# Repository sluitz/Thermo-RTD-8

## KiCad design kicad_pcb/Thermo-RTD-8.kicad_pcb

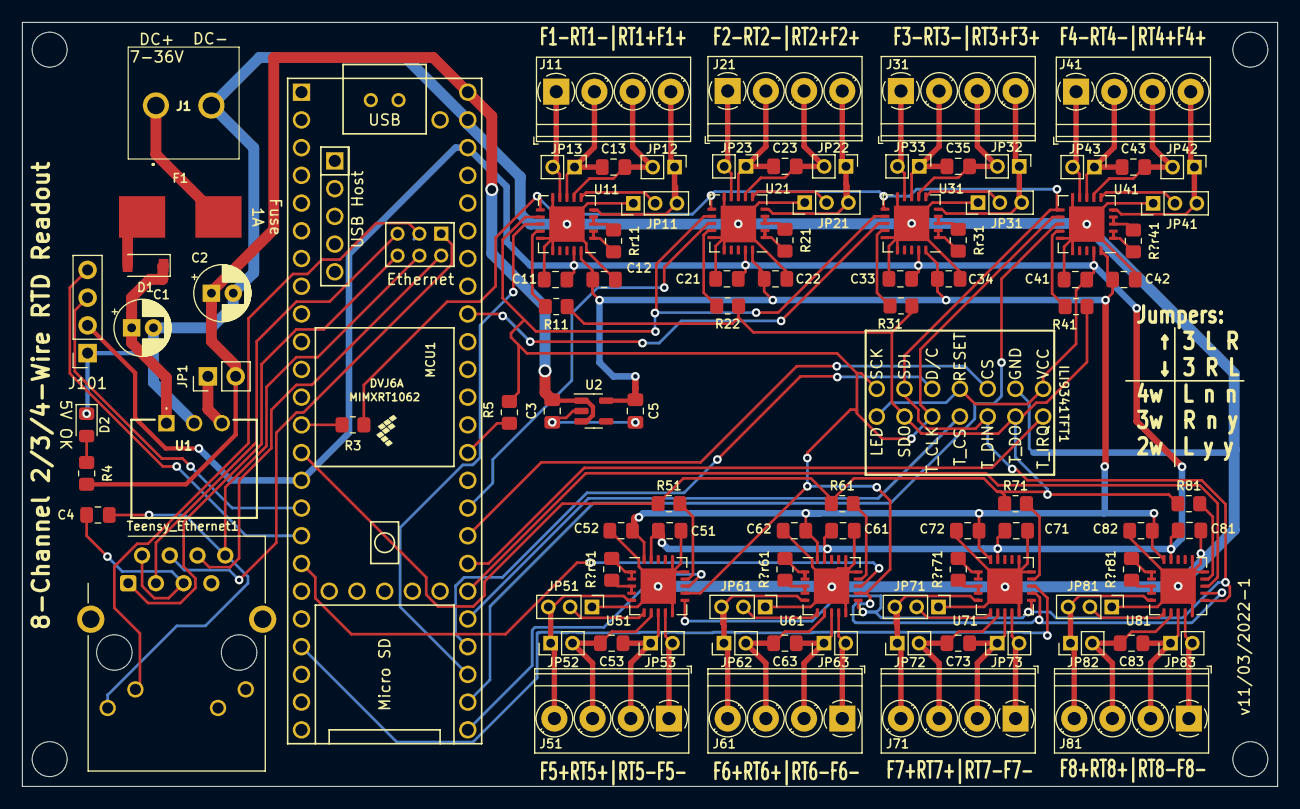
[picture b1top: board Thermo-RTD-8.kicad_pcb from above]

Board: 2 copper layers, 115.0 x 70.0 mm, 103 parts (0 on the bottom side), 99 nets.

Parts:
C1: 10u; CP_Radial_D5.0mm_P2.00mm
C2: 22u; CP_Radial_D5.0mm_P2.00mm
C3, C5: 1u; C_0805_2012Metric_Pad1.18x1.45mm_HandSolder
C4, C11, C12, C13, C21, C22, C23, C33, C34, C35, C41, C42, C43, C51, C52, C53, C61, C62, C63, C71, C72, C73, C81, C82, C83: 100n; C_0805_2012Metric_Pad1.18x1.45mm_HandSolder
D1: D; D_SOD-123
D2: LED 5VOK; LED_0805_2012Metric_Pad1.15x1.40mm_HandSolder
F1: 1A; smd_fuse
H1, H2, H3, H4: MountingHole; MountingHole_3.2mm_M3_DIN965
ILI9341TFT1: ILI9341TFT-RibbonCable
J1: Screw_Terminal_01x02; TB00750802BE
J11, J21, J31, J41, J51, J61, J71, J81: Ch1; TerminalBlock_Phoenix_PT-1,5-4-3.5-H_1x04_P3.50mm_Horizontal
J101: OLED Display I2C; PinSocket_1x04_P2.54mm_Vertical
JP1: PS; PinHeader_1x02_P2.54mm_Vertical
JP11, JP21, JP31, JP41, JP51, JP61, JP71, JP81: 3w:2+3; PinHeader_1x03_P2.00mm_Vertical
JP12, JP22, JP32, JP42, JP52, JP62, JP72, JP82: 2w; PinHeader_1x02_P2.00mm_Vertical
JP13, JP23, JP33, JP43, JP53, JP63, JP73, JP83: 2/3w; PinHeader_1x02_P2.00mm_Vertical
MCU1: Teensy41
R3, R5, R11, R22, R31, R41, R51, R61, R71, R81: 22R; R_0805_2012Metric_Pad1.20x1.40mm_HandSolder
R4: 330R; R_0805_2012Metric_Pad1.20x1.40mm_HandSolder
R21: 440R; R_0805_2012Metric_Pad1.20x1.40mm_HandSolder
R?r41, R?r51, R?r61, R?r71, R?r81: 440R; R_0805_2012Metric_Pad1.20x1.40mm_HandSolder
Rr11, Rr31: 440R; R_0805_2012Metric_Pad1.20x1.40mm_HandSolder
Teensy_Ethernet1: RJ45_Cetus_J1B1211CCD_Horizontal
U1: N7805; N78051C
U2: NCP163ASN330T1G; SOT-23-5
U11, U21, U31, U41, U51, U61, U71, U81: MAX31865xTP; TQFN-20-1EP_5x5mm_P0.65mm_EP3.25x3.25mm

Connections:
+3.3V: C11.2, C21.2, C33.2, C41.2, C51.2, C61.2, C71.2, C81.2, ILI9341TFT1.1, ILI9341TFT1.4, ILI9341TFT1.8, J101.2, MCU1.15 (3V3), MCU1.46 (3V3), U11.19 (DVDD), U21.19 (DVDD), U31.19 (DVDD), U41.19 (DVDD), U51.19 (DVDD), U61.19 (DVDD), U71.19 (DVDD), U81.19 (DVDD)
+3.3VA: C5.1, C12.1, C22.1, C34.1, C42.1, C52.1, C62.1, C72.1, C82.1, U2.5 (VOUT), U11.20 (VDD), U21.20 (VDD), U31.20 (VDD), U41.20 (VDD), U51.20 (VDD), U61.20 (VDD), U71.20 (VDD), U81.20 (VDD)
+5V: C2.1, C3.1, JP1.2 (B), MCU1.48 (VIN), R4.1, U2.1 (VIN), U2.3 (EN)
/CLK: ILI9341TFT1.7, ILI9341TFT1.10, R5.1, U11.12 (SCLK), U21.12 (SCLK), U31.12 (SCLK), U41.12 (SCLK), U51.12 (SCLK), U61.12 (SCLK), U71.12 (SCLK), U81.12 (SCLK)
/CS_1: MCU1.27 (35_TX8), U11.13 (~CS)
/CS_2: MCU1.33 (41_A17), U21.13 (~CS)
/CS_3: MCU1.40 (18_A4_SDA), U31.13 (~CS)
/CS_4: MCU1.26 (34_RX8), U41.13 (~CS)
/CS_5: MCU1.25 (33_MCLK2), U51.13 (~CS)
/CS_6: MCU1.18 (26_A12_MOSI1), U61.13 (~CS)
/CS_7: MCU1.21 (29_TX7), U71.13 (~CS)
/CS_8: MCU1.30 (38_CS1_IN1), U81.13 (~CS)
/SDI: ILI9341TFT1.6, ILI9341TFT1.12, R3.2, U11.11 (SDI), U21.11 (SDI), U31.11 (SDI), U41.11 (SDI), U51.11 (SDI), U61.11 (SDI), U71.11 (SDI), U81.11 (SDI)
/SDO: ILI9341TFT1.9, ILI9341TFT1.13, MCU1.14 (12_MISO_MQSL), R11.1, R22.1, R31.1, R41.1, R51.1, R61.1, R71.1, R81.1
/TFT_CS: ILI9341TFT1.3, MCU1.32 (40_A16)
/TFT_DC: ILI9341TFT1.5, MCU1.28 (36_CS)
/T_CS: ILI9341TFT1.11, MCU1.29 (37_CS)
/T_IRQ: ILI9341TFT1.14, MCU1.31 (39_MISO1_OUT1A)
GND: C1.2, C2.2, C3.2, C5.2, C11.1, C12.2, C21.1, C22.2, C33.1, C34.2, C41.1, C42.2, C51.1, C52.2, C61.1, C62.2, C71.1, C72.2, C81.1, C82.2, D2.1 (K), ILI9341TFT1.2, J1.2, J101.1, JP11.1 (A), JP21.1 (A), JP31.1 (A), JP41.1 (A), JP51.1 (A), JP61.1 (A), JP71.1 (A), JP81.1 (A), MCU1.47 (GND), U1.2 (GND/-Vout), U2.2 (GND), U11.10 (GND), U11.15 (DGND), U11.16 (GND), U11.21 (GND), U21.10 (GND), U21.15 (DGND), U21.16 (GND), U21.21 (GND), U31.10 (GND), U31.15 (DGND), U31.16 (GND), U31.21 (GND), U41.10 (GND), U41.15 (DGND), U41.16 (GND), U41.21 (GND), U51.10 (GND), U51.15 (DGND), U51.16 (GND), U51.21 (GND), U61.10 (GND), U61.15 (DGND), U61.16 (GND), U61.21 (GND), U71.10 (GND), U71.15 (DGND), U71.16 (GND), U71.21 (GND), U81.10 (GND), U81.15 (DGND), U81.16 (GND), U81.21 (GND)
I2C_SCL: J101.3, MCU1.16 (24_A10_TX6_SCL2)
I2C_SDA: J101.4, MCU1.17 (25_A11_RX6_SDA2)
unnamed: C1.1, D1.1 (K), U1.1 (IN)
unnamed: C4.1, Teensy_Ethernet1.2, Teensy_Ethernet1.5
unnamed: C4.2, MCU1.64 (GND), Teensy_Ethernet1.8, Teensy_Ethernet1.9
unnamed: C13.1, J11.2, JP13.1 (A), U11.8 (RTDIN-)
unnamed: C13.2, J11.3, JP12.2 (B), U11.7 (RTDIN+)
unnamed: C23.1, J21.2, JP23.1 (A), U21.8 (RTDIN-)
unnamed: C23.2, J21.3, JP22.2 (B), U21.7 (RTDIN+)
unnamed: C35.1, J31.2, JP33.1 (A), U31.8 (RTDIN-)
unnamed: C35.2, J31.3, JP32.2 (B), U31.7 (RTDIN+)
unnamed: C43.1, J41.2, JP43.1 (A), U41.8 (RTDIN-)
unnamed: C43.2, J41.3, JP42.2 (B), U41.7 (RTDIN+)
unnamed: C53.1, J51.2, JP53.1 (A), U51.8 (RTDIN-)
unnamed: C53.2, J51.3, JP52.2 (B), U51.7 (RTDIN+)
unnamed: C63.1, J61.2, JP63.1 (A), U61.8 (RTDIN-)
unnamed: C63.2, J61.3, JP62.2 (B), U61.7 (RTDIN+)
unnamed: C73.1, J71.2, JP73.1 (A), U71.8 (RTDIN-)
unnamed: C73.2, J71.3, JP72.2 (B), U71.7 (RTDIN+)
unnamed: C83.1, J81.2, JP83.1 (A), U81.8 (RTDIN-)
unnamed: C83.2, J81.3, JP82.2 (B), U81.7 (RTDIN+)
unnamed: D1.2 (A), F1.1
unnamed: D2.2 (A), R4.2
unnamed: F1.2, J1.1
unnamed: J11.1, JP13.2 (B), U11.9 (FORCE-)
unnamed: J11.4, JP11.3 (B), JP12.1 (A), U11.5 (FORCE+)
unnamed: J21.1, JP23.2 (B), U21.9 (FORCE-)
unnamed: J21.4, JP21.3 (B), JP22.1 (A), U21.5 (FORCE+)
unnamed: J31.1, JP33.2 (B), U31.9 (FORCE-)
unnamed: J31.4, JP31.3 (B), JP32.1 (A), U31.5 (FORCE+)
unnamed: J41.1, JP43.2 (B), U41.9 (FORCE-)
unnamed: J41.4, JP41.3 (B), JP42.1 (A), U41.5 (FORCE+)
unnamed: J51.1, JP53.2 (B), U51.9 (FORCE-)
unnamed: J51.4, JP51.3 (B), JP52.1 (A), U51.5 (FORCE+)
unnamed: J61.1, JP63.2 (B), U61.9 (FORCE-)
unnamed: J61.4, JP61.3 (B), JP62.1 (A), U61.5 (FORCE+)
unnamed: J71.1, JP73.2 (B), U71.9 (FORCE-)
unnamed: J71.4, JP71.3 (B), JP72.1 (A), U71.5 (FORCE+)
unnamed: J81.1, JP83.2 (B), U81.9 (FORCE-)
unnamed: J81.4, JP81.3 (B), JP82.1 (A), U81.5 (FORCE+)
unnamed: JP1.1 (A), U1.3 (+Vout/GND)
unnamed: JP11.2 (C), U11.6 (FORCE2)
unnamed: JP21.2 (C), U21.6 (FORCE2)
unnamed: JP31.2 (C), U31.6 (FORCE2)
unnamed: JP41.2 (C), U41.6 (FORCE2)
unnamed: JP51.2 (C), U51.6 (FORCE2)
unnamed: JP61.2 (C), U61.6 (FORCE2)
unnamed: JP71.2 (C), U71.6 (FORCE2)
unnamed: JP81.2 (C), U81.6 (FORCE2)
unnamed: MCU1.13 (11_MOSI_CTX1), R3.1
unnamed: MCU1.35 (13_SCK_LED), R5.2
unnamed: MCU1.60 (R+), Teensy_Ethernet1.4
unnamed: MCU1.61 (LED), Teensy_Ethernet1.10
unnamed: MCU1.62 (T-), Teensy_Ethernet1.3
unnamed: MCU1.63 (T+), Teensy_Ethernet1.1
unnamed: MCU1.65 (R-), Teensy_Ethernet1.6
unnamed: R11.2, U11.14 (SDO)
unnamed: R21.1, U21.1 (BIAS), U21.2 (REFIN+)
unnamed: R21.2, U21.3 (REFIN-), U21.4 (ISENSOR)
unnamed: R22.2, U21.14 (SDO)
unnamed: R31.2, U31.14 (SDO)
unnamed: R41.2, U41.14 (SDO)
unnamed: R51.2, U51.14 (SDO)
unnamed: R61.2, U61.14 (SDO)
unnamed: R71.2, U71.14 (SDO)
unnamed: R81.2, U81.14 (SDO)
unnamed: R?r41.1, U41.1 (BIAS), U41.2 (REFIN+)
unnamed: R?r41.2, U41.3 (REFIN-), U41.4 (ISENSOR)
unnamed: R?r51.1, U51.1 (BIAS), U51.2 (REFIN+)
unnamed: R?r51.2, U51.3 (REFIN-), U51.4 (ISENSOR)
unnamed: R?r61.1, U61.1 (BIAS), U61.2 (REFIN+)
unnamed: R?r61.2, U61.3 (REFIN-), U61.4 (ISENSOR)
unnamed: R?r71.1, U71.1 (BIAS), U71.2 (REFIN+)
unnamed: R?r71.2, U71.3 (REFIN-), U71.4 (ISENSOR)
unnamed: R?r81.1, U81.1 (BIAS), U81.2 (REFIN+)
unnamed: R?r81.2, U81.3 (REFIN-), U81.4 (ISENSOR)
unnamed: Rr11.1, U11.1 (BIAS), U11.2 (REFIN+)
unnamed: Rr11.2, U11.3 (REFIN-), U11.4 (ISENSOR)
unnamed: Rr31.1, U31.1 (BIAS), U31.2 (REFIN+)
unnamed: Rr31.2, U31.3 (REFIN-), U31.4 (ISENSOR)

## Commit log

2022-12-02 Thermo-RTD-8 initial commit
